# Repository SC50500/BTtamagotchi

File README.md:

# ARIRANG

# Description
A 4-button tamagotchi remix based on global pop band BTS's new album "ARIRANG" featuring a speaker in place of a buzzer and unique tamagotchi dancing emoticons. Instead of indicating changes in the pet's state using buzzes, the ARIRANG tamagotchi uses a sequence of notes from the speaker to play a familiar tune. What makes this tamagotchi design unique is that it uses easily accessible parts and produces sound from the speaker without storage of music on a micro-SD card or similar component. Music is played through using the tone() function in the Arduino IDE. 

# Purpose
The basic eat, sleep, and play functions of your average tamagotchi are still present in this design, allowing users to interact with their tamagotchi pet at any time of day. An additional music feature has been added to the tamagotchi, as coded for by the fourth button on the PCB. This button plays one of three tunes, extrapolated from popular BTS songs and inspired by piano or music box covers arranged by other composers and artists (View credits for more information). 

For more information about what a tamagotchi is and how to use it, check out [this guide](https://tamagotchi.fandom.com/wiki/Main_Page) on what a tamagotchi is. 

# Inspiration
As someone who has been a fan of BTS since they were 7 years old, I've dreamed of completing a project that allowed me to take creative liberty in designing a product that reflected both my interest in KPOP and engineering.
The theme of the tamagotchi was centered around "ARIRANG", BTS's newest album that was recently released this year. After being inactive as a band for over 3 years, this was the long-awaited "comeback" album that myself and other long-time fans were excited to listen to.
More importantly, this album holds a different meaning to the fandom, ARMY, and the group; It is meant to represent a return to the roots from which BTS first came.
So, in honor of their return from their hiatus, I decided to dedicate my first hardware project to them -- A band whose songs motivated me throughout all of the obstacles I overcame to ship this project. 

# Features
* **0.96" OLED Display (128 x 64):** Black and white, yes, but perfect for Van, a character that is monochromatic ;3
* **INGHAi Speaker:** A small, but powerful speaker with a simple adapter that allows for music from Arduino IDE or bluetooth to be played. 
* **Four tactile switches:** The first three are for the basic eat, sleep, and play functions of the tamagotchi, but the fourth is a "music" button that activates one of three tunes that any BTS fan would recognize, paired with a pet dancing animation.
* **Unique themed pet and animations:** Your tamagotchi pet goes by the name Van! Van is a character from the LINE x BTS collaboration, which produced a line of BTS mascots called BT21. In this collaboration, Van represents the ARMY, BTS's fandom, instead of a specific member. I felt that because of this, Van was the most suitable mascot for this project. 

# How does this work? 
Each of the four different buttons are mapped to one of four screens: eat, play, sleep, and dance/music.

* Left-up button: For when Van is feeling a bit peckish
* Left-down button: For when Van is bored
* Right-up button: For when Van needs some rest
* Right-down button: For when Van is ready to party :3

When these buttons are pressed, a quick transition music is played to indicate a change in Van's status. If any of Van's status bars (Hunger, Happiness, and Energy) fall below 50, Van's expression will change into a sad expression. 

After each animation runs its course, the screen returns back to the main screen while the pet awaits further instruction.

# Design
Below are all of the screenshots of my design (plus screenshots by layer and an exploded view :3)

# Bill of Materials

| Item | Unit Price | Quantity Used | Quantity Purchased | Total Price | Source | Notes |
|---|---|---|---|---|---|---|
| Seeed Studio XIAO ESP32-C3 | $9.90 | 1 | 1 | $9.90 | [Link](https://www.amazon.com/dp/B0B94JZ2YF?lv=shuf&hvlocphy=97766&linkCode=df0&hvnetw=o&hvadid=80195839596273&hvbmt=be&hvdev=c&hvocijid=11735809307987410767-B0DRNSV5CS-&hvqmt=e&hvexpln=0&tag=bingshoppinga-20&hvtargid=pla-4583795321231844&channelId=69&ref_=asc_df_B0DRNSV5CS&plpRedirect=mhFallback&th=1) | purchased with other items off Amazon; free shipping |
| HS96L03W2C03 | $2.24 | 1 | 1 | $2.24 | [Link](https://www.lcsc.com/product-detail/C5248080.html?spm=wm.gwc.xh.0.cbm___wm.fly.ssl.gwc&lcsc_vid=EwNbXlIEQQMIXlYDTlYPAQdXEVhXXlMARARfUwdRRwAxVlNeRVFeVlBUTlBeXjsOAxUeFF5JWBYZEEoKFBINSQcJGk4eFQsCAgIaSgADAwAHC0slRVlWX1BfRE8GEwkK) | shipping not included |
| INGHAi GSPK2307P-8R1W | $0.82 | 1 | 1 | $0.82 | [Link](https://www.lcsc.com/product-detail/Speakers_INGHAi-GSPK2307P-8R1W_C530531.html) | shipping not included |
| PAM8302AAYCR | $9.37 | 1 | 1 | $9.37 | [Link](https://www.digikey.com/en/products/detail/diodes-incorporated/PAM8302AAYCR/4033367?gclid=b27fbcf56e80137c3cb2d6c241cebef9&gclsrc=3p.ds&msclkid=b27fbcf56e80137c3cb2d6c241cebef9) | shipping included |
| BZCN TSC016A04518A | $0.04 | 4 | 50 | $0.54 | [Link](https://www.lcsc.com/product-detail/C2888493.html?s_z=h_q_C2888493&globalKeyword=C2888493) | shipping not included |
| UNIT 502030 D9 - 250mAh 3.7V 0.93Wh | $8.99 | 1 | 1 | $8.99 | [Link](https://www.amazon.com/dp/B08FD3V6TF?lv=shuf&channelId=520&plpRedirect=mhFallback) | shipping not included |
| TAMAGOTCHI PCB | $2.00 | 1 | 5 | $2.00 | [Link](https://cart.jlcpcb.com/shopcart/cart/) | first PCB is $2.00; no shipping fee or taxes (Global standard line) |
| M3 x 8mm Pozi Pan Head Screws | $0.09 | 2 | 20 | $0.99 | [Link](https://www.aliexpress.us/item/3256807955659503.html?spm=a2g0o.productlist.main.1.570fYl0xYl0xWq&algo_pvid=98fb9b49-47a3-4173-a920-562ea71ffb80) | not 1:1 to the attached CAD; but can still be used; shipping not included |
| M2 x 8mm Pozi Pan Head Screws | $0.20 | 4 | 20 | $0.99 | [Link](https://www.aliexpress.us/item/3256807955659503.html?spm=a2g0o.productlist.main.1.570fYl0xYl0xWq&algo_pvid=98fb9b49-47a3-4173-a920-562ea71ffb80) | not 1:1 to the attached CAD; but can still be used; shipping not included |
| *AMAZON SHIPPING & TAXES* |  |  |  | *$9.29* |  | ONLY shipping fees and taxes for all products purchased through Amazon |
| *LCSC SHIPPING & TAXES* |  |  |  | *$10.65* |  | ONLY shipping fees and taxes for all products purchased through LCSC |
| *ALIEXPRESS SHIPPING & TAXES* |  |  |  | *$4.09* |  | ONLY shipping fees and taxes for all products purchased through AliExpress |
| **TOTAL** |  |  |  | **$53.80** |  |  |

# Build & Assembly

## Required Tools

- Soldering iron
- Solder
- Tweezers
- Small screwdriver for M3 screws
- Computer with USB port
- 3D printer

## Assembly Steps

1. Solder all the THT diodes onto the PCB
2. Solder the LEDs to the PCB. I rotated the direction of the bottom row by accident so refer to the PCB layout if the orientation is confusing at all
3. Solder the microcontroller, OLED display, and switches to the PCB
4. To assemble the case, place the PCB into the bottom shell
5. Attach it to the top shell
6. Secure with M3 screws.
7. Since this build uses the ESP32-C3, I will use the ESPRESSIF Arduino IDE Extension to install firmware
8. Plug in the ESP32-C3 to your computer with a USB cable
9. Select the correct board and port in the Arduino IDE, then upload the firmware
10. Modify the code if you'd like to change Van's animations or tune selection
11. Test your OLED (check I2C, SDA/SCL pins, etc) and your speaker
12. Once everything works, you will have a fully functional Van!

# Credits & Acknowledgements

Credits to BTS's new "ARIRANG" album cover and the BTS ARMY Logo for the hardware design inspiration. 

## Libraries & Extensions Used

Libraries and extensions used in firmware
* ESPRESSIF Arduino IDE Extension
* Adafruit SSD1306
* Adafruit GFX Library

## Music Attribution & Copyright Disclaimer
The audio files included in this repository are piano covers intended for non-commercial entertainment purposes only.

*    *Original Composition:* "Crystal Snow", "Spring Day", and "Butterfly", intitially performed by BTS, copyrighted by Big Hit Music / HYBE. 
*    *Arrangements:* Based on the piano arrangements by [SMYANG PIANO](https://www.youtube.com/c/smyangpiano) (used with pending permission.
*    *Performances:* Recorded and arranged by Sophia Chan.

*Disclaimer: Although the music used in the tamagotchi are inspired by the music box and piano arrangements created by SMYANG PIANO as a cover for BTS's music, the actual arrangements slightly differ in composition.*

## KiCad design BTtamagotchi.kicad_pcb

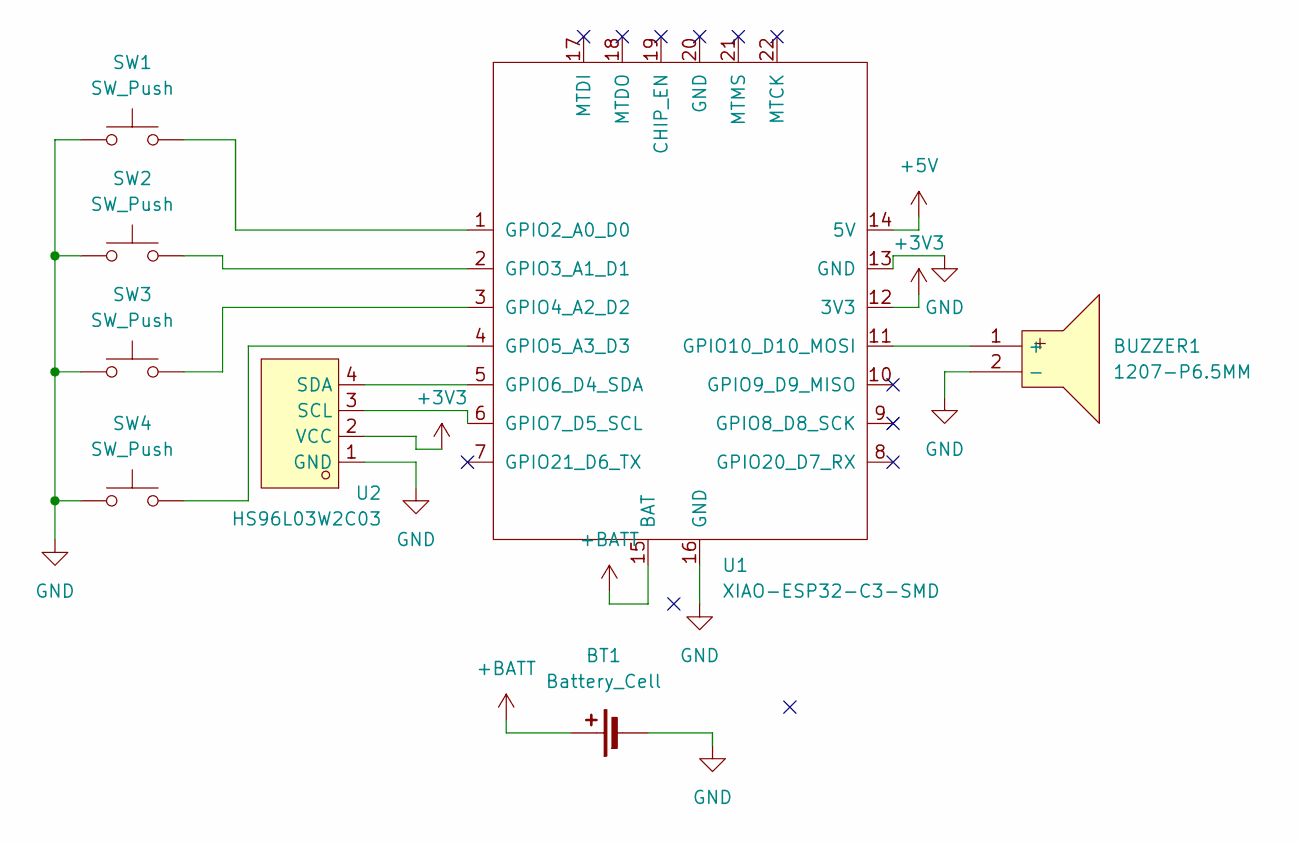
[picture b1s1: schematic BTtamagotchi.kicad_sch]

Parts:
BT1: Battery_Cell; PinHeader_1x02_P2.54mm_Vertical
BUZZER1: 1207-P6.5MM; BUZ-TH_BD12.5-P6.50-D1.4; MPN 1207-P6.5MM; LCSC Part C49246964
SW1, SW2, SW3, SW4: SW_Push; SW-TH_4P-L4.5-W4.5-P3.00-LS4.8
U1: XIAO-ESP32-C3-SMD; XIAO-ESP32-C3-DIP-SMD
U2: HS96L03W2C03; OLED-TH_L27.8-W27.2-P2.54_C9900033791; MPN HS96L03W2C03; LCSC Part C5248080

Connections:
+3V3: U1.12 (3V3), U2.2 (VCC)
+5V: U1.14 (5V)
+BATT: BT1.1 (+), U1.15 (BAT)
GND: BT1.2 (-), BUZZER1.2 (-), SW1.1, SW2.1, SW3.1, SW4.1, U1.13 (GND), U1.16 (GND), U2.1 (GND)
unnamed: BUZZER1.1 (+), U1.11 (GPIO10_D10_MOSI)
unnamed: SW1.2, U1.1 (GPIO2_A0_D0)
unnamed: SW2.2, U1.2 (GPIO3_A1_D1)
unnamed: SW3.2, U1.3 (GPIO4_A2_D2)
unnamed: SW4.2, U1.4 (GPIO5_A3_D3)
unnamed: U1.5 (GPIO6_D4_SDA), U2.4 (SDA)
unnamed: U1.6 (GPIO7_D5_SCL), U2.3 (SCL)

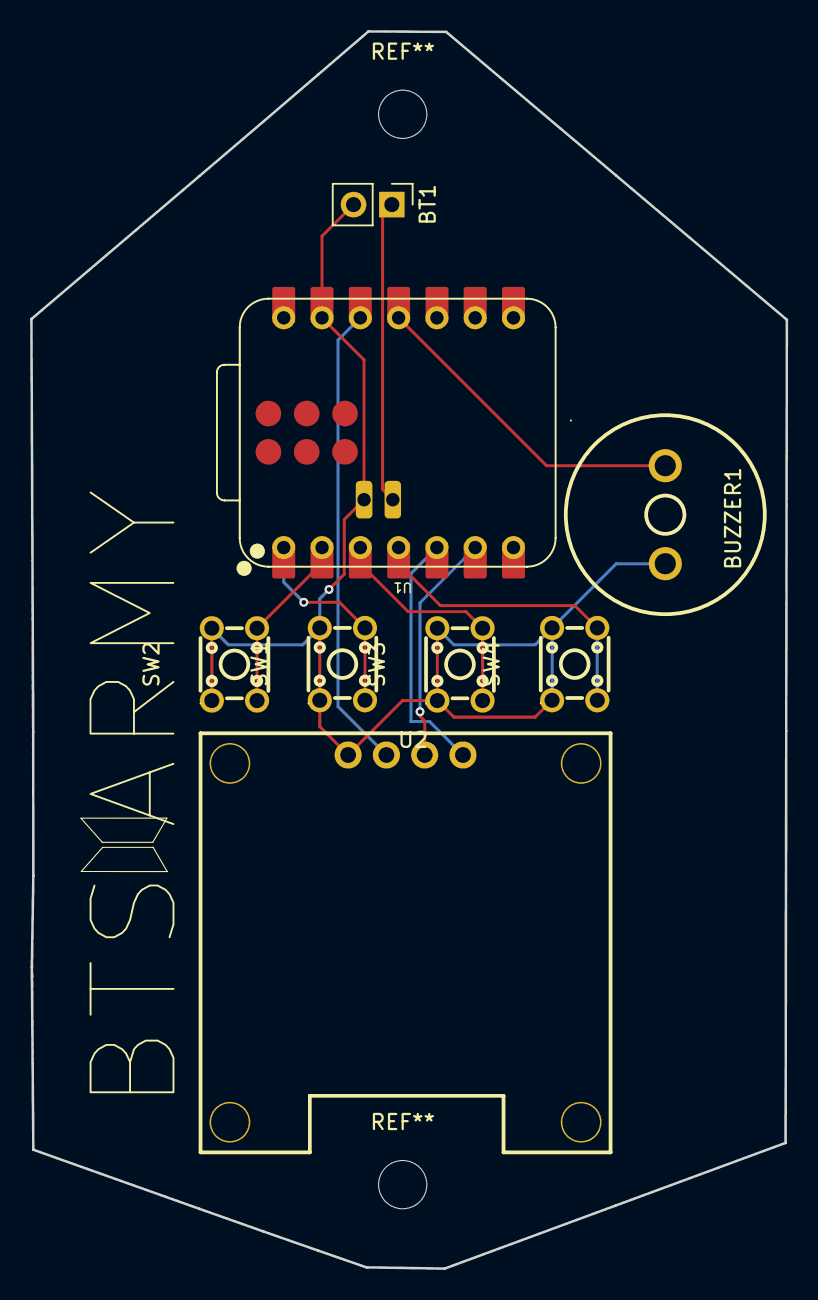
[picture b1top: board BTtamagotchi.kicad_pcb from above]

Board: 2 copper layers, 50.1 x 82.1 mm, 8 parts (0 on the bottom side), 10 nets.

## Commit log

2026-06-21 Update BOM.csv
    done for now?
2026-06-21 Update BOM.csv
    fixed
2026-06-21 Create fhnhfn
2026-06-21 Create grbrs
2026-06-21 Changed folders
2026-06-21 FINAL COMMIT
2026-06-21 FINAL FINAL COMMIT
2026-06-21 changed zine
2026-06-21 changed name of firmware file
2026-06-21 file names and readme changes
2026-06-25 updated zine
